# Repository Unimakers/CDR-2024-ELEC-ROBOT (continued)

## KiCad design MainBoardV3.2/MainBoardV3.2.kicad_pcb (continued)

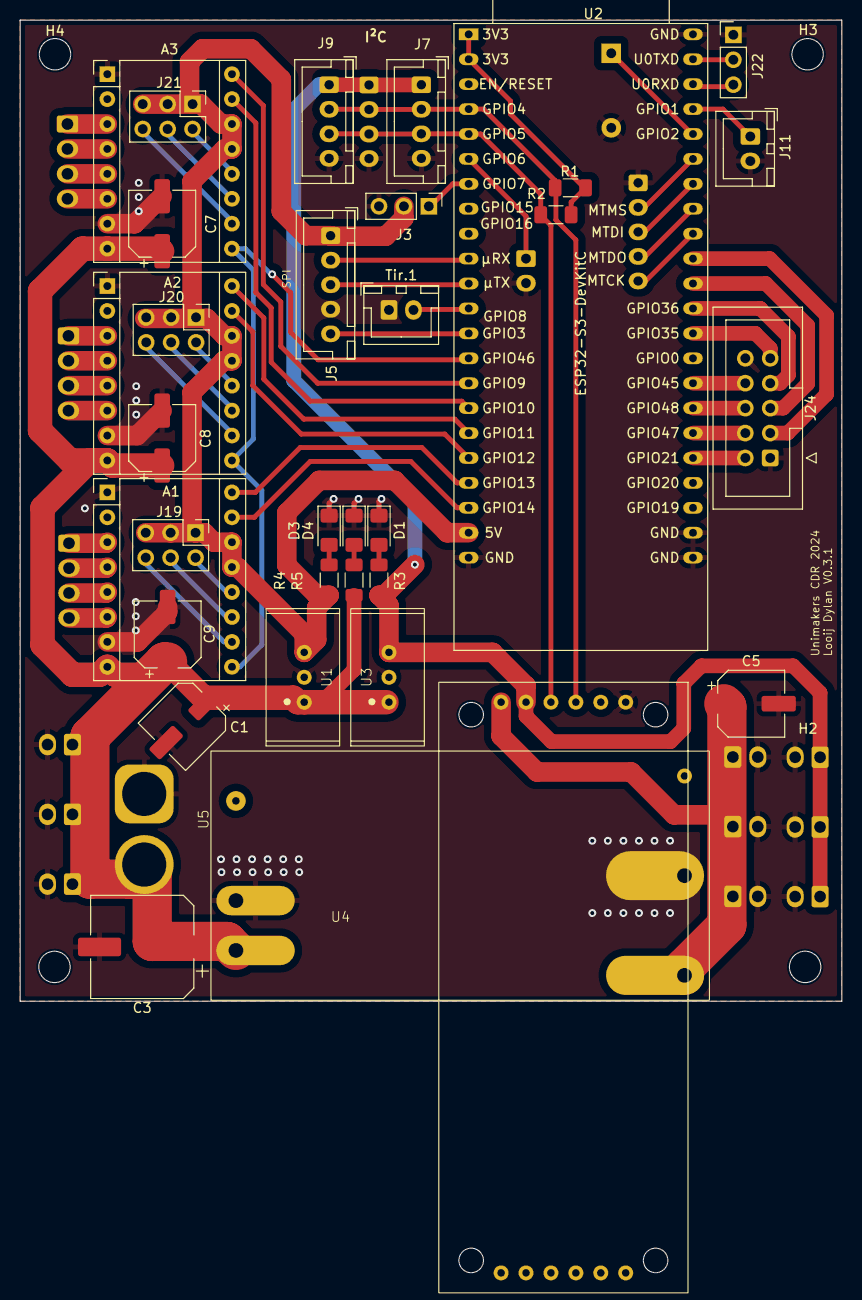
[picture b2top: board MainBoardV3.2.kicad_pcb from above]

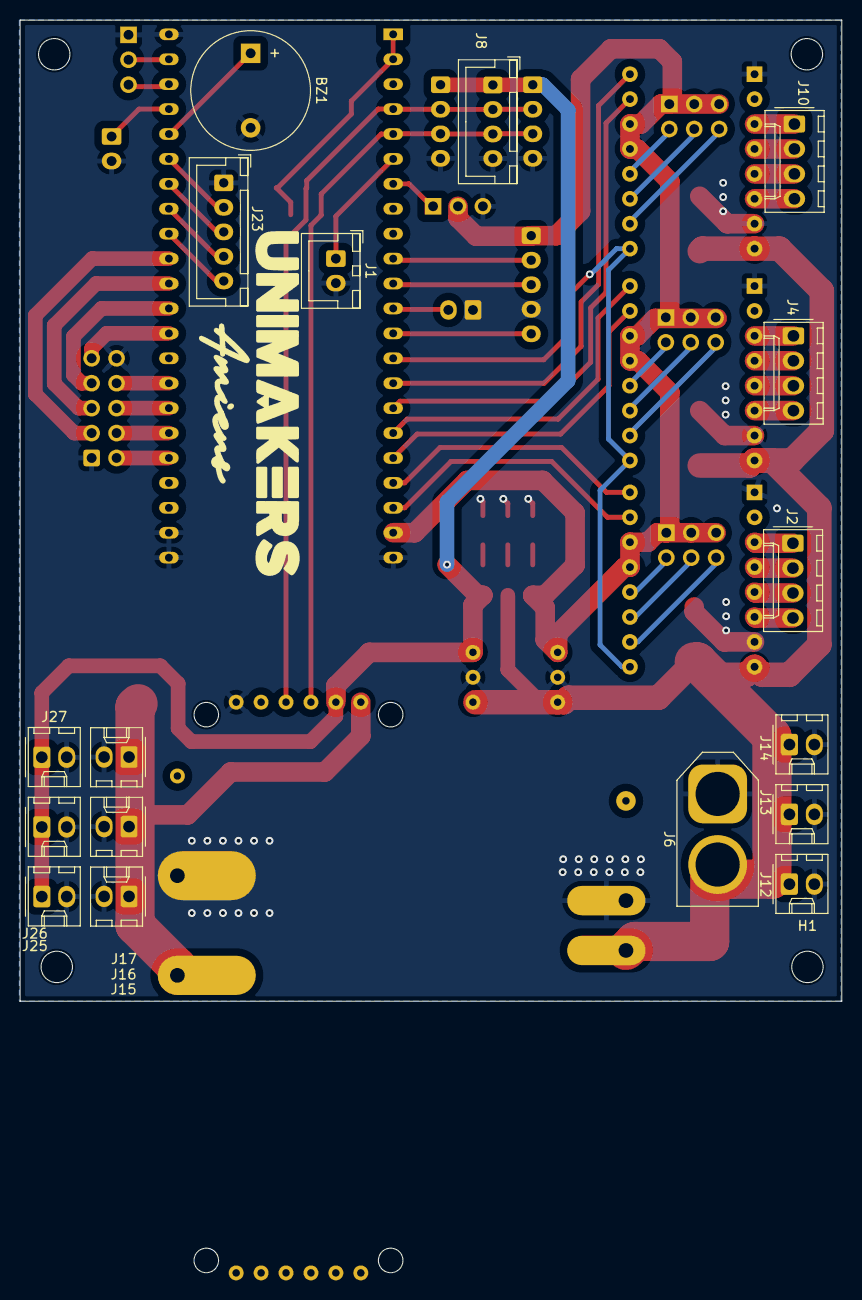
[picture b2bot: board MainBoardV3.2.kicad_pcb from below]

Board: 2 copper layers, 83.7 x 100.0 mm, 54 parts (18 on the bottom side), 61 nets.

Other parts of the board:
A2: Pololu_Breakout_DRV8825; Pololu_Breakout-16_15.2x20.3mm
D1, D3: LED_Small; LED_1206_3216Metric_Pad1.42x1.75mm_HandSolder
R3, R4: R_Small; R_1206_3216Metric_Pad1.30x1.75mm_HandSolder

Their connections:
DIR2: A2.16 (DIR); also elsewhere on the board
EN: A2.9 (~EN); also elsewhere on the board
GND: A2.1 (GND), A2.7 (GND), D1.1 (K), D3.1 (K); also elsewhere on the board
unnamed 28: A2.4 (A1); also elsewhere on the board
unnamed 29: A2.3 (A2); also elsewhere on the board
unnamed 30: A2.5 (B1); also elsewhere on the board
unnamed 31: A2.6 (B2); also elsewhere on the board
unnamed 32: A2.10 (M0); also elsewhere on the board
unnamed 33: A2.11 (M1); also elsewhere on the board
unnamed 34: A2.12 (M2); also elsewhere on the board
unnamed: D1.2 (A), R3.2
unnamed: D3.2 (A), R4.2
STEP2: A2.15 (STEP); also elsewhere on the board

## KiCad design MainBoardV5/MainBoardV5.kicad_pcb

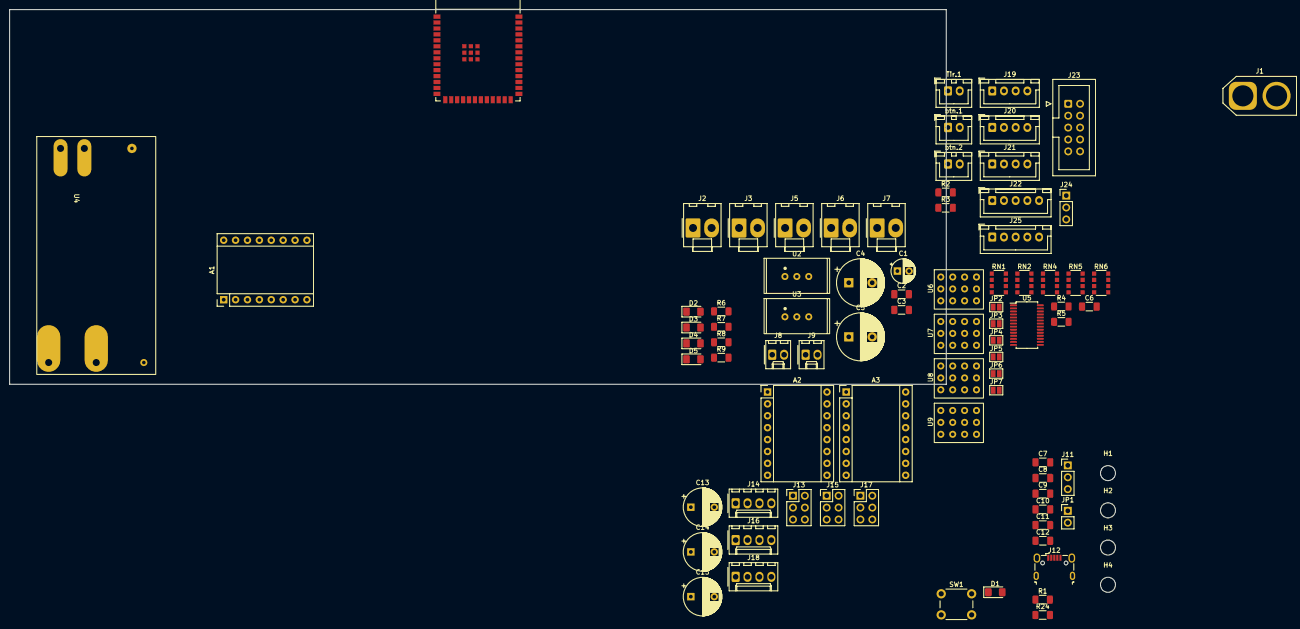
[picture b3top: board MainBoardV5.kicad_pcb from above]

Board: 4 copper layers, 200.0 x 80.0 mm, 85 parts (0 on the bottom side), 104 nets, no tracks yet.

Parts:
A1, A2, A3: Pololu_Breakout_DRV8825; Pololu_Breakout-16_15.2x20.3mm
C1: C_Polarized; CP_Radial_D5.0mm_P2.50mm
C2, C3, C6: C_Small; C_1206_3216Metric_Pad1.33x1.80mm_HandSolder
C4, C5: C_Polarized; CP_Radial_D10.0mm_P5.00mm
C7, C8, C9, C10, C11, C12: C; C_1206_3216Metric_Pad1.33x1.80mm_HandSolder
C13, C14, C15: C_Polarized; CP_Radial_D8.0mm_P5.00mm
D1, D2, D3, D4, D5: LED_Small; LED_1206_3216Metric_Pad1.42x1.75mm_HandSolder
H1, H2, H3, H4: MountingHole; MountingHole_3.2mm_M3
J1: Conn_01x02; AMASS_XT60-M_1x02_P7.20mm_Vertical
J2, J3, J5, J6, J7: Conn_01x02; Molex_KK-396_A-41791-0002_1x02_P3.96mm_Vertical
J8, J9: Conn_01x02; Molex_KK-254_AE-6410-02A_1x02_P2.54mm_Vertical
J11, J24: Conn_01x03; PinHeader_1x03_P2.54mm_Vertical
J12: USB_B_Micro; USB_Micro-B_Wuerth_629105150521
J13, J15, J17: Conn_02x03_Odd_Even; PinHeader_2x03_P2.54mm_Vertical
J14, J16, J18: Conn_01x04; Molex_KK-254_AE-6410-04A_1x04_P2.54mm_Vertical
J19, J20, J21: Conn_01x04; JST_XH_B4B-XH-A_1x04_P2.50mm_Vertical
J22, J25: Conn_01x05; JST_XH_B5B-XH-A_1x05_P2.50mm_Vertical
J23: Conn_02x05_Odd_Even; IDC-Header_2x05_P2.54mm_Vertical
JP1: Jumper_2_Open; PinHeader_1x02_P2.54mm_Vertical
JP2, JP3, JP4, JP5, JP6, JP7: Jumper_2_Open; SolderJumper-2_P1.3mm_Open_Pad1.0x1.5mm
R1, R4, R5, R6, R7, R8, R9: R_Small; R_1206_3216Metric_Pad1.30x1.75mm_HandSolder
R2, R3, R24: R; R_1206_3216Metric_Pad1.30x1.75mm_HandSolder
RN1, RN2, RN4, RN5, RN6: R_Pack04; R_Array_Convex_4x1206
SW1: SW_Push; SW_PUSH_6mm
Tir.1: Conn_01x02; JST_XH_B2B-XH-A_1x02_P2.50mm_Vertical
U1: ESP32-S3-WROOM-1
U2: TSR_2-2433; Traco 2- 24xx
U3: TSR_2-2450; Traco 2- 24xx
U4: TEN_50-2411WI; Traco TEN 50 series
U5: PCA9685PW; TSSOP-28_4.4x9.7mm_P0.65mm
U6, U7, U8, U9: Servo_Conn_Pack_x04; Servo_Bloc_x04
btn.1, btn.2: Conn_01x02; JST_XH_B2B-XH-A_1x02_P2.50mm_Vertical

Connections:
+3.3V: C6.2, J19.1, J20.1, J21.1, JP2.1 (A), JP3.1 (A), JP4.1 (A), JP5.1 (A), JP6.1 (A), JP7.1 (A), R2.1, R3.1, U5.28 (VDD)
+3V3: C2.1, C9.1, C10.1, R6.1, R24.1, U1.2 (3V3), U2.3 (VO)
+5V: A1.13 (~RST), A1.14 (~SLP), A2.13 (~RST), A2.14 (~SLP), A3.13 (~RST), A3.14 (~SLP), C3.1, J8.2, J9.2, J13.1, J13.3, J13.5, J15.1, J15.3, J15.5, J17.1, J17.3, J17.5, J22.1, R7.1, U3.3 (VO)
+5VP: C5.1, J5.2, J6.2, J7.2, J24.2, R8.1, U4.4 (+Vout), U6.1 (VCC), U7.1 (VCC), U8.1 (VCC), U9.1 (VCC)
+BATT: A1.8 (VMOT), A2.8 (VMOT), A3.8 (VMOT), C1.1, C4.1, C13.1, C14.1, C15.1, J1.2, J2.2, J3.2, R9.1, U2.1 (VI), U3.1 (VI), U4.1 (+Vin)
/Micro Proccessor/en: C11.1, C12.1, R24.2, SW1.2, U1.3 (EN)
Btn1: U1.5 (GPIO5/TOUCH5/ADC1_CH4), btn.1.2
Btn2: U1.6 (GPIO6/TOUCH6/ADC1_CH5), btn.2.2
DIR1: A1.16 (DIR), U1.20 (GPIO12/TOUCH12/ADC2_CH1/FSPICLK/FSPIIO6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)
DIR2: A2.16 (DIR), U1.18 (GPIO10/TOUCH10/ADC1_CH9/FSPICS0/FSPIIO4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)
DIR3: A3.16 (DIR), U1.15 (GPIO3/TOUCH3/ADC1_CH2)
EN: A1.9 (~EN), A2.9 (~EN), A3.9 (~EN), U1.22 (GPIO14/TOUCH14/ADC2_CH3/FSPIWP/FSPIDQS/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)
GND: A1.1 (GND), A1.7 (GND), A2.1 (GND), A2.7 (GND), A3.1 (GND), A3.7 (GND), C1.2, C2.2, C3.2, C4.2, C5.2, C6.1, C7.2, C8.2, C9.2, C10.2, C11.2, C12.2, C13.2, C14.2, C15.2, D1.1 (K), D2.1 (K), D3.1 (K), D4.1 (K), D5.1 (K), J1.1, J2.1, J3.1, J5.1, J6.1, J7.1, J8.1, J9.1, J11.3, J12.5 (GND), J12.6 (Shield), J19.4, J20.4, J21.4, J22.4, J23.1, J23.10, J24.3, J25.1, JP1.2 (B), R4.2, R5.2, RN2.1 (R1.1), RN2.2 (R2.1), RN2.3 (R3.1), RN2.4 (R4.1), SW1.1, Tir.1.1, U1.1 (GND), U1.40 (GND), U1.41 (GND), U2.2 (GND), U3.2 (GND), U4.2 (-Vin), U4.5 (-Vout), U5.14 (VSS), U5.25 (EXTCLK), U6.2 (GND), U7.2 (GND), U8.2 (GND), U9.2 (GND), btn.1.1, btn.2.1
LIDARRX: J22.2, U1.10 (GPIO17/U1TXD/ADC2_CH6)
LIDARTX: J22.3, U1.11 (GPIO18/U1RXD/ADC2_CH7/CLK_OUT3)
Nappe1: J23.8, U1.39 (GPIO1/TOUCH1/ADC1_CH0)
Nappe2: J23.6, U1.38 (GPIO2/TOUCH2/ADC1_CH1)
Nappe3: J23.4, U1.31 (GPIO38/FSPIWP/SUBSPIWP)
Nappe4: J23.2, U1.30 (SPIDQS/GPIO37/FSPIQ/SUBSPIQ)
Nappe5: J23.9, U1.25 (GPIO48/SPICLK_N/SUBSPICLK_N_DIFF)
Nappe6: J23.7, U1.26 (GPIO45)
Nappe7: J23.5, U1.28 (SPIIO6/GPIO35/FSPID/SUBSPID)
Nappe8: J23.3, U1.29 (SPIIO7/GPIO36/FSPICLK/SUBSPICLK)
Neopixel: J24.1, U1.7 (GPIO7/TOUCH7/ADC1_CH6)
unnamed: A1.4 (A1), J14.2
unnamed: A1.3 (A2), J14.1
unnamed: A1.5 (B1), J14.3
unnamed: A1.6 (B2), J14.4
unnamed: A1.10 (M0), J13.6
unnamed: A1.11 (M1), J13.4
unnamed: A1.12 (M2), J13.2
unnamed: A2.4 (A1), J16.2
unnamed: A2.3 (A2), J16.1
unnamed: A2.5 (B1), J16.3
unnamed: A2.6 (B2), J16.4
unnamed: A2.10 (M0), J15.6
unnamed: A2.11 (M1), J15.4
unnamed: A2.12 (M2), J15.2
unnamed: A3.4 (A1), J18.2
unnamed: A3.3 (A2), J18.1
unnamed: A3.5 (B1), J18.3
unnamed: A3.6 (B2), J18.4
unnamed: A3.10 (M0), J17.6
unnamed: A3.11 (M1), J17.4
unnamed: A3.12 (M2), J17.2
unnamed: D1.2 (A), R1.1
unnamed: D2.2 (A), R6.2
unnamed: D3.2 (A), R7.2
unnamed: D4.2 (A), R8.2
unnamed: D5.2 (A), R9.2
unnamed: J11.1, U1.37 (U0TXD/GPIO43/CLK_OUT1)
unnamed: J11.2, U1.36 (U0RXD/GPIO44/CLK_OUT2)
unnamed: C8.1, J12.3 (D+), U1.14 (GPIO20/U1CTS/ADC2_CH9/CLK_OUT1/USB_D+)
unnamed: C7.1, J12.2 (D-), U1.13 (GPIO19/U1RTS/ADC2_CH8/CLK_OUT2/USB_D-)
unnamed: J12.1 (VBUS), R1.2
unnamed: JP1.1 (A), U1.27 (GPIO0/BOOT)
unnamed: JP2.2 (B), RN2.8 (R1.2), U5.1 (A0)
unnamed: JP3.2 (B), RN2.7 (R2.2), U5.2 (A1)
unnamed: JP4.2 (B), RN2.6 (R3.2), U5.3 (A2)
unnamed: JP5.2 (B), RN2.5 (R4.2), U5.4 (A3)
unnamed: JP6.2 (B), R4.1, U5.5 (A4)
unnamed: JP7.2 (B), R5.1, U5.24 (A5)
unnamed: RN1.1 (R1.1), U5.9 (LED3)
unnamed: RN1.8 (R1.2), U6.6 (Servo1)
unnamed: RN1.2 (R2.1), U5.8 (LED2)
unnamed: RN1.7 (R2.2), U6.5 (Servo1)
unnamed: RN1.3 (R3.1), U5.7 (LED1)
unnamed: RN1.6 (R3.2), U6.4 (Servo1)
unnamed: RN1.4 (R4.1), U5.6 (LED0)
unnamed: RN1.5 (R4.2), U6.3 (Servo1)
unnamed: RN4.1 (R1.1), U5.13 (LED7)
unnamed: RN4.8 (R1.2), U7.6 (Servo1)
unnamed: RN4.2 (R2.1), U5.12 (LED6)
unnamed: RN4.7 (R2.2), U7.5 (Servo1)
unnamed: RN4.3 (R3.1), U5.11 (LED5)
unnamed: RN4.6 (R3.2), U7.4 (Servo1)
unnamed: RN4.4 (R4.1), U5.10 (LED4)
unnamed: RN4.5 (R4.2), U7.3 (Servo1)
unnamed: RN5.1 (R1.1), U5.18 (LED11)
unnamed: RN5.8 (R1.2), U8.6 (Servo1)
unnamed: RN5.2 (R2.1), U5.17 (LED10)
unnamed: RN5.7 (R2.2), U8.5 (Servo1)
unnamed: RN5.3 (R3.1), U5.16 (LED9)
unnamed: RN5.6 (R3.2), U8.4 (Servo1)
unnamed: RN5.4 (R4.1), U5.15 (LED8)
unnamed: RN5.5 (R4.2), U8.3 (Servo1)
unnamed: RN6.1 (R1.1), U5.22 (LED15)
unnamed: RN6.8 (R1.2), U9.6 (Servo1)
unnamed: RN6.2 (R2.1), U5.21 (LED14)
unnamed: RN6.7 (R2.2), U9.5 (Servo1)
unnamed: RN6.3 (R3.1), U5.20 (LED13)
unnamed: RN6.6 (R3.2), U9.4 (Servo1)
unnamed: RN6.4 (R4.1), U5.19 (LED12)
unnamed: RN6.5 (R4.2), U9.3 (Servo1)
SCL: J19.2, J20.2, J21.2, R2.2, U1.17 (GPIO9/TOUCH9/ADC1_CH8/FSPIHD/SUBSPIHD), U5.26 (SCL)
SDA: J19.3, J20.3, J21.3, R3.2, U1.12 (GPIO8/TOUCH8/ADC1_CH7/SUBSPICS1), U5.27 (SDA)
SPICLK: J25.2, U1.32 (MTCK/GPIO39/CLK_OUT3/SUBSPICS1)
SPIDI: J25.4, U1.34 (MTDI/GPIO41/CLK_OUT1)
SPIDO: J25.3, U1.33 (MTDO/GPIO40/CLK_OUT2)
SPIMS: J25.5, U1.35 (MTMS/GPIO42)
STEP1: A1.15 (STEP), U1.21 (GPIO13/TOUCH13/ADC2_CH2/FSPIQ/FSPIIO7/S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)
STEP2: A2.15 (STEP), U1.19 (GPIO11/TOUCH11/ADC2_CH0/FSPID/FSPIIO5/S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)
STEP3: A3.15 (STEP), U1.16 (GPIO46)
Tir.: Tir.1.2, U1.4 (GPIO4/TOUCH4/ADC1_CH3)

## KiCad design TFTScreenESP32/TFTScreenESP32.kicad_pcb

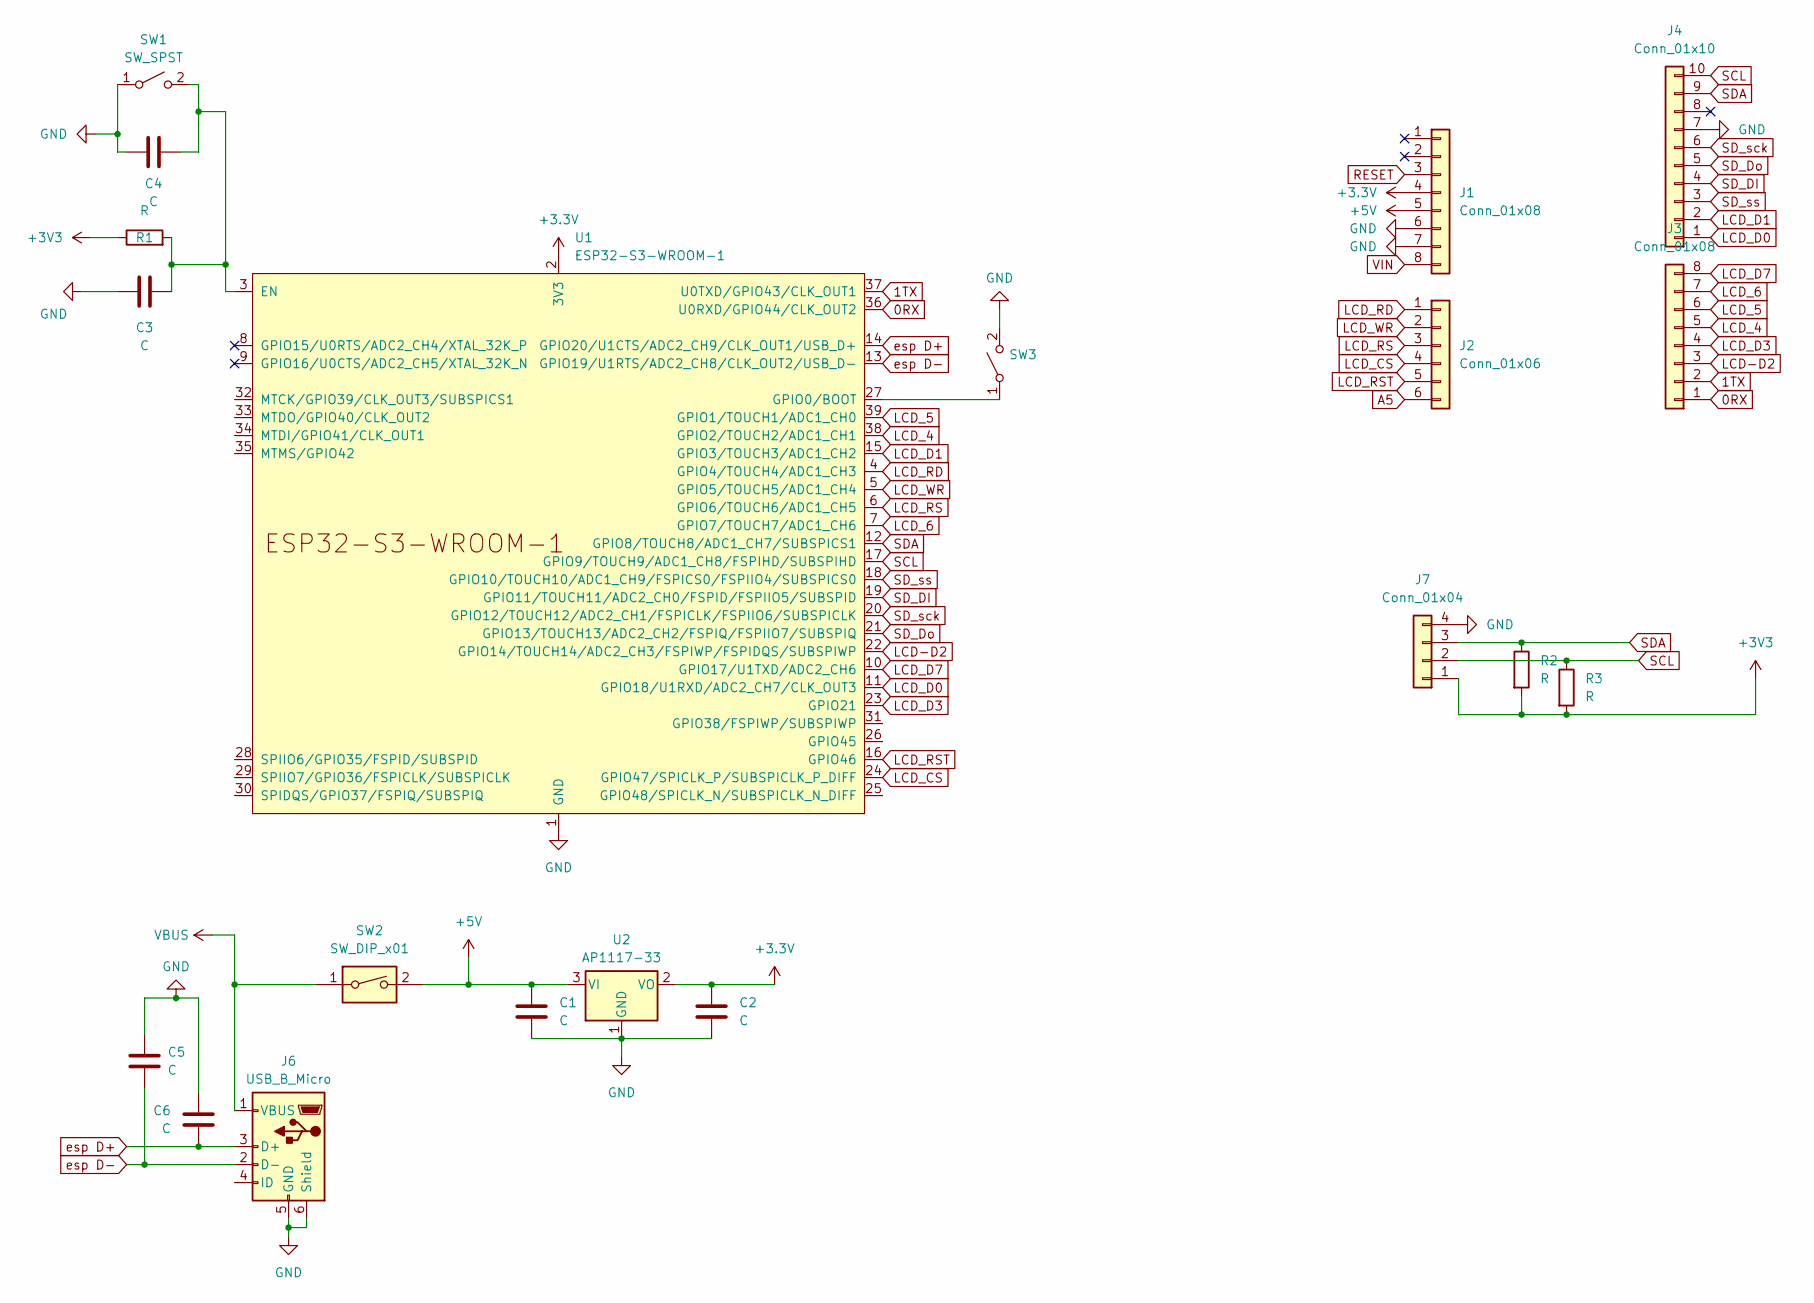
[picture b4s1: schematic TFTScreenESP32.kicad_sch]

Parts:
C1, C2, C3, C4, C5, C6: C; C_1206_3216Metric_Pad1.33x1.80mm_HandSolder
J1, J3: Conn_01x08; PinSocket_1x08_P2.54mm_Vertical
J2: Conn_01x06; PinSocket_1x06_P2.54mm_Vertical
J4: Conn_01x10; PinSocket_1x10_P2.54mm_Vertical
J6: USB_B_Micro; USB_Micro-B_Molex-105017-0001
J7: Conn_01x04; JST_XH_B4B-XH-A_1x04_P2.50mm_Vertical
R1, R2, R3: R; R_1206_3216Metric_Pad1.30x1.75mm_HandSolder
SW1, SW3: SW_SPST; PinSocket_1x02_P2.54mm_Vertical
SW2: SW_DIP_x01; SW_DIP_SPSTx01_Slide_9.78x4.72mm_W7.62mm_P2.54mm
U1: ESP32-S3-WROOM-1
U2: AP1117-33; SOT-223-3_TabPin2

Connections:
0RX: J3.1, U1.36 (U0RXD/GPIO44/CLK_OUT2)
1TX: J3.2, U1.37 (U0TXD/GPIO43/CLK_OUT1)
+5V: C1.1, J1.5, SW2.2, U2.3 (VI)
A5: J2.6
GND: C1.2, C2.2, C3.2, C4.2, C5.2, C6.1, J1.6, J1.7, J4.7, J6.5 (GND), J6.6 (Shield), J7.4, SW1.1 (A), SW3.2 (B), U1.1 (GND), U1.40 (GND), U1.41 (GND), U2.1 (GND)
LCD-D2: J3.3, U1.22 (GPIO14/TOUCH14/ADC2_CH3/FSPIWP/FSPIDQS/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)
LCD_4: J3.5, U1.38 (GPIO2/TOUCH2/ADC1_CH1)
LCD_5: J3.6, U1.39 (GPIO1/TOUCH1/ADC1_CH0)
LCD_6: J3.7, U1.7 (GPIO7/TOUCH7/ADC1_CH6)
LCD_CS: J2.4, U1.24 (GPIO47/SPICLK_P/SUBSPICLK_P_DIFF)
LCD_D0: J4.1, U1.11 (GPIO18/U1RXD/ADC2_CH7/CLK_OUT3)
LCD_D1: J4.2, U1.15 (GPIO3/TOUCH3/ADC1_CH2)
LCD_D3: J3.4, U1.23 (GPIO21)
LCD_D7: J3.8, U1.10 (GPIO17/U1TXD/ADC2_CH6)
LCD_RD: J2.1, U1.4 (GPIO4/TOUCH4/ADC1_CH3)
LCD_RS: J2.3, U1.6 (GPIO6/TOUCH6/ADC1_CH5)
LCD_RST: J2.5, U1.16 (GPIO46)
LCD_WR: J2.2, U1.5 (GPIO5/TOUCH5/ADC1_CH4)
unnamed: C3.1, C4.1, R1.2, SW1.2 (B), U1.3 (EN)
unnamed: SW3.1 (A), U1.27 (GPIO0/BOOT)
RESET: J1.3
SCL: J4.10, J7.2, R3.1, U1.17 (GPIO9/TOUCH9/ADC1_CH8/FSPIHD/SUBSPIHD)
SDA: J4.9, J7.3, R2.1, U1.12 (GPIO8/TOUCH8/ADC1_CH7/SUBSPICS1)
SD_DI: J4.4, U1.19 (GPIO11/TOUCH11/ADC2_CH0/FSPID/FSPIIO5/S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)
SD_Do: J4.5, U1.21 (GPIO13/TOUCH13/ADC2_CH2/FSPIQ/FSPIIO7/S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)
SD_sck: J4.6, U1.20 (GPIO12/TOUCH12/ADC2_CH1/FSPICLK/FSPIIO6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)
SD_ss: J4.3, U1.18 (GPIO10/TOUCH10/ADC1_CH9/FSPICS0/FSPIIO4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)
VBUS: J6.1 (VBUS), SW2.1
VIN: J1.8
esp D+: C6.2, J6.3 (D+), U1.14 (GPIO20/U1CTS/ADC2_CH9/CLK_OUT1/USB_D+)
esp D-: C5.1, J6.2 (D-), U1.13 (GPIO19/U1RTS/ADC2_CH8/CLK_OUT2/USB_D-)

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
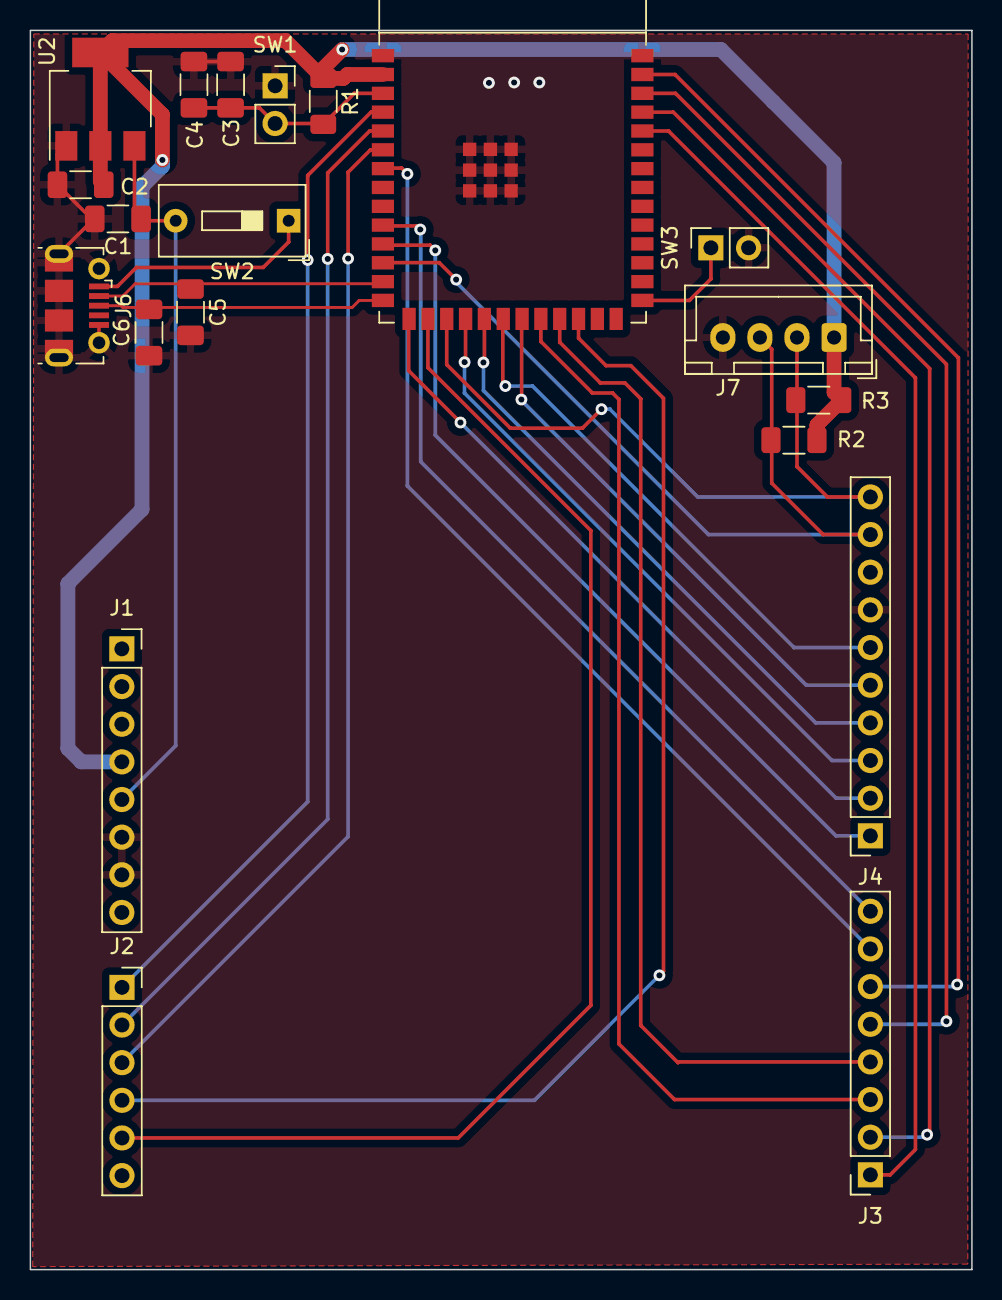
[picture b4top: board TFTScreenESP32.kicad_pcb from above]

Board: 2 copper layers, 63.5 x 83.6 mm, 20 parts (0 on the bottom side), 29 nets.

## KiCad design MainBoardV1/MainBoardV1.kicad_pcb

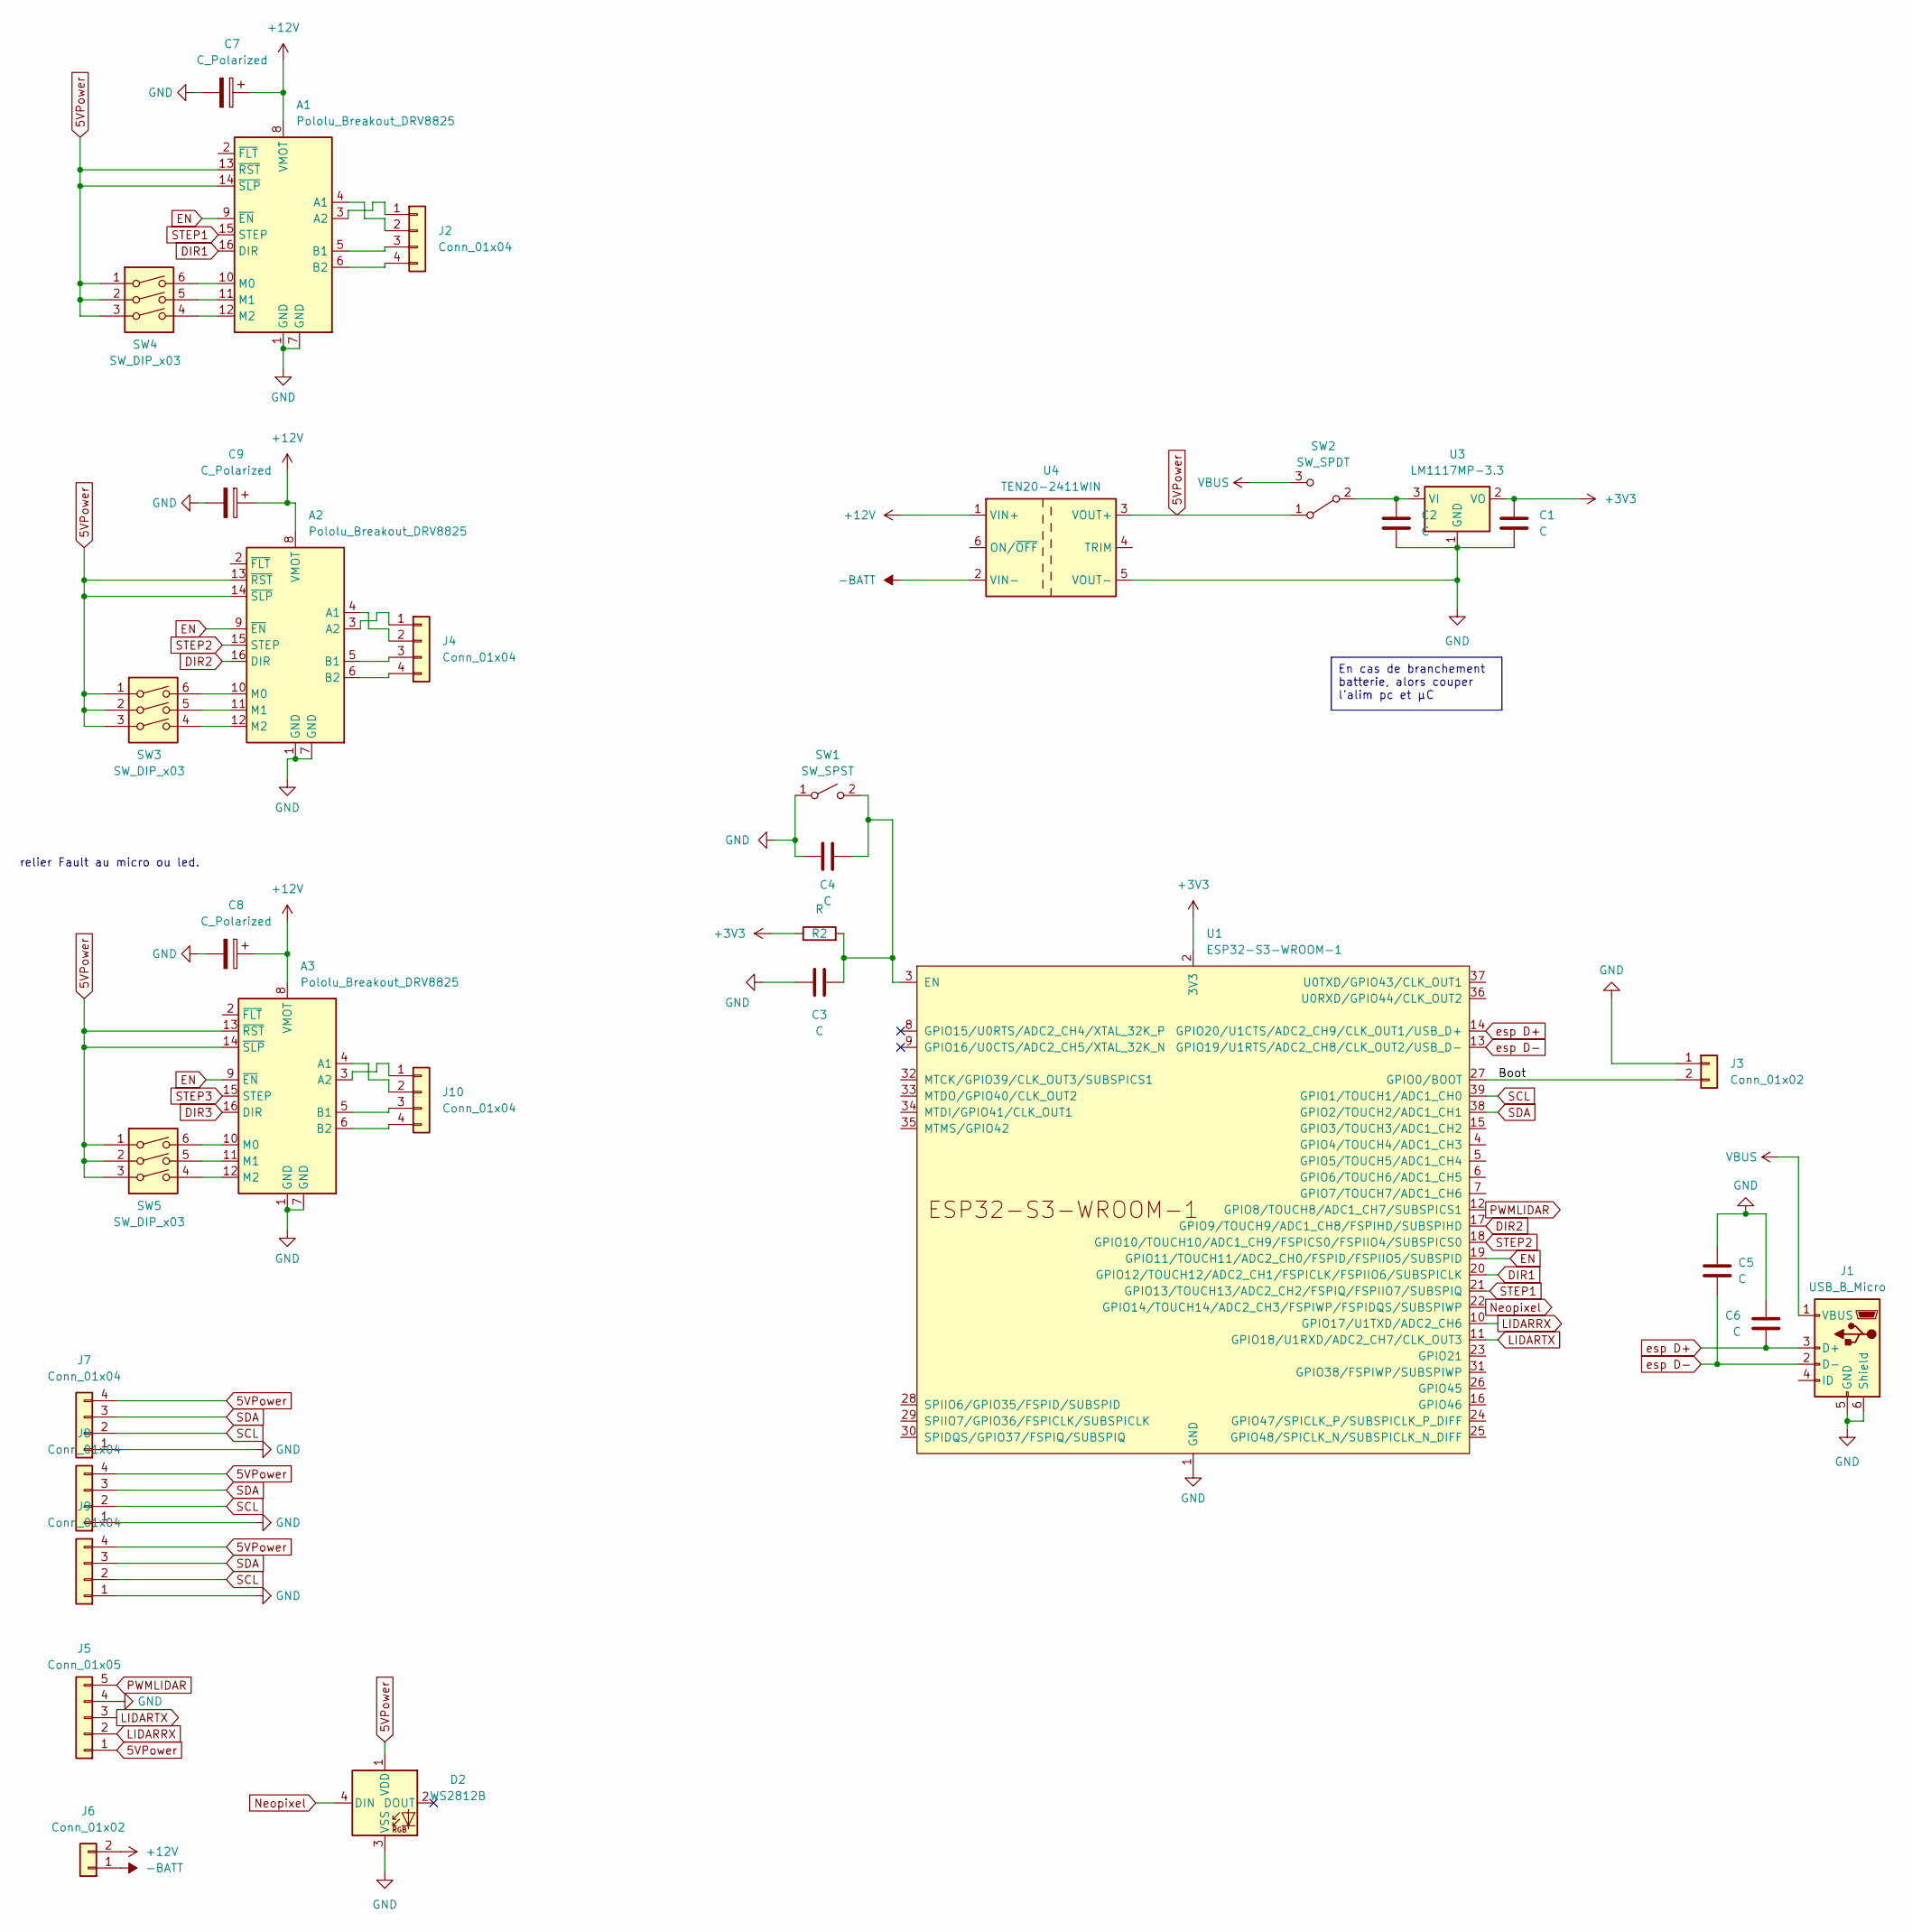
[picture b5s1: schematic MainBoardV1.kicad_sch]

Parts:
A1, A2, A3: Pololu_Breakout_DRV8825; Pololu_Breakout-16_15.2x20.3mm
C1, C2, C3, C4, C5, C6: C; C_1206_3216Metric_Pad1.33x1.80mm_HandSolder
C7, C8, C9: C_Polarized; CP_Radial_D8.0mm_P3.50mm
D2: WS2812B; LED_WS2812B_PLCC4_5.0x5.0mm_P3.2mm
J1: USB_B_Micro; USB_Micro-B_Molex-105017-0001
J2, J4, J7, J8, J9, J10: Conn_01x04; JST_XH_B4B-XH-A_1x04_P2.50mm_Vertical
J3: Conn_01x02; PinHeader_1x02_P2.54mm_Vertical
J5: Conn_01x05; JST_XH_B5B-XH-A_1x05_P2.50mm_Vertical
J6: Conn_01x02; TerminalBlock_Altech_AK300-2_P5.00mm
R2: R; R_1206_3216Metric_Pad1.30x1.75mm_HandSolder
SW1: SW_SPST; PinSocket_1x02_P2.54mm_Vertical
SW2: SW_SPDT; PinSocket_1x03_P2.54mm_Vertical
SW3, SW4, SW5: SW_DIP_x03; SW_DIP_SPSTx03_Slide_9.78x9.8mm_W8.61mm_P2.54mm
U1: ESP32-S3-WROOM-1
U3: LM1117MP-3.3; SOT-223-3_TabPin2
U4: TEN20-2411WIN; Converter_DCDC_TRACO_TEN20-xxxx_THT

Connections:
5VPower: A1.13 (~RST), A1.14 (~SLP), A2.13 (~RST), A2.14 (~SLP), A3.13 (~RST), A3.14 (~SLP), D2.1 (VDD), J5.1, J7.4, J8.4, J9.4, SW2.1 (A), SW3.1, SW3.2, SW3.3, SW4.1, SW4.2, SW4.3, SW5.1, SW5.2, SW5.3, U4.3 (VOUT+)
+3V3: C1.1, R2.1, U1.2 (3V3), U3.2 (VO)
+12V: A1.8 (VMOT), A2.8 (VMOT), A3.8 (VMOT), C7.1, C8.1, C9.1, J6.2, U4.1 (VIN+)
-BATT: J6.1, U4.2 (VIN-)
/Boot: J3.2, U1.27 (GPIO0/BOOT)
DIR1: A1.16 (DIR), U1.20 (GPIO12/TOUCH12/ADC2_CH1/FSPICLK/FSPIIO6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)
DIR2: A2.16 (DIR), U1.17 (GPIO9/TOUCH9/ADC1_CH8/FSPIHD/SUBSPIHD)
DIR3: A3.16 (DIR)
EN: A1.9 (~EN), A2.9 (~EN), A3.9 (~EN), U1.19 (GPIO11/TOUCH11/ADC2_CH0/FSPID/FSPIIO5/S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)
GND: A1.1 (GND), A1.7 (GND), A2.1 (GND), A2.7 (GND), A3.1 (GND), A3.7 (GND), C1.2, C2.2, C3.2, C4.2, C5.2, C6.1, C7.2, C8.2, C9.2, D2.3 (VSS), J1.5 (GND), J1.6 (Shield), J3.1, J5.4, J7.1, J8.1, J9.1, SW1.1 (A), U1.1 (GND), U1.40 (GND), U1.41 (GND), U3.1 (GND), U4.5 (VOUT-)
LIDARRX: J5.2, U1.10 (GPIO17/U1TXD/ADC2_CH6)
LIDARTX: J5.3, U1.11 (GPIO18/U1RXD/ADC2_CH7/CLK_OUT3)
Neopixel: D2.4 (DIN), U1.22 (GPIO14/TOUCH14/ADC2_CH3/FSPIWP/FSPIDQS/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)
unnamed: A1.4 (A1), J2.2
unnamed: A1.3 (A2), J2.1
unnamed: A1.5 (B1), J2.3
unnamed: A1.6 (B2), J2.4
unnamed: A1.10 (M0), SW4.6
unnamed: A1.11 (M1), SW4.5
unnamed: A1.12 (M2), SW4.4
unnamed: A2.4 (A1), J4.2
unnamed: A2.3 (A2), J4.1
unnamed: A2.5 (B1), J4.3
unnamed: A2.6 (B2), J4.4
unnamed: A2.10 (M0), SW3.6
unnamed: A2.11 (M1), SW3.5
unnamed: A2.12 (M2), SW3.4
unnamed: A3.4 (A1), J10.2
unnamed: A3.3 (A2), J10.1
unnamed: A3.5 (B1), J10.3
unnamed: A3.6 (B2), J10.4
unnamed: A3.10 (M0), SW5.6
unnamed: A3.11 (M1), SW5.5
unnamed: A3.12 (M2), SW5.4
unnamed: C3.1, C4.1, R2.2, SW1.2 (B), U1.3 (EN)
unnamed: C2.1, SW2.2 (B), U3.3 (VI)
PWMLIDAR: J5.5, U1.12 (GPIO8/TOUCH8/ADC1_CH7/SUBSPICS1)
SCL: J7.2, J8.2, J9.2, U1.39 (GPIO1/TOUCH1/ADC1_CH0)
SDA: J7.3, J8.3, J9.3, U1.38 (GPIO2/TOUCH2/ADC1_CH1)
STEP1: A1.15 (STEP), U1.21 (GPIO13/TOUCH13/ADC2_CH2/FSPIQ/FSPIIO7/S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)
STEP2: A2.15 (STEP), U1.18 (GPIO10/TOUCH10/ADC1_CH9/FSPICS0/FSPIIO4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)
STEP3: A3.15 (STEP)
VBUS: J1.1 (VBUS), SW2.3 (C)
esp D+: C6.2, J1.3 (D+), U1.14 (GPIO20/U1CTS/ADC2_CH9/CLK_OUT1/USB_D+)
esp D-: C5.1, J1.2 (D-), U1.13 (GPIO19/U1RTS/ADC2_CH8/CLK_OUT2/USB_D-)

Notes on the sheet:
En cas de branchement batterie, alors couper l'alim pc et µC
relier Fault au micro ou led.

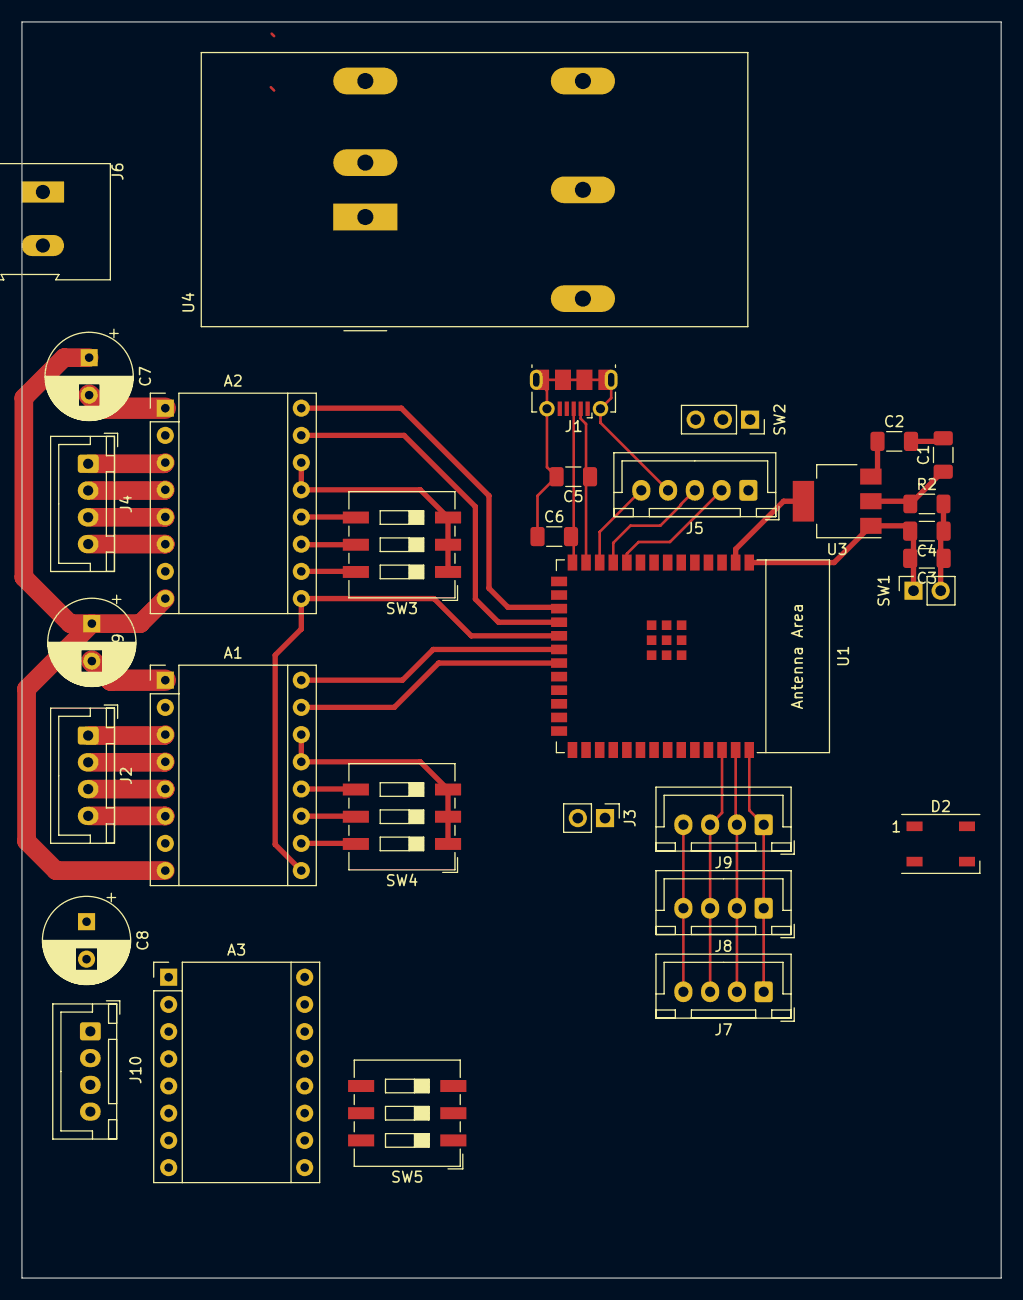
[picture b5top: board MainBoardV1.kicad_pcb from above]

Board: 2 copper layers, 91.4 x 117.3 mm, 32 parts (0 on the bottom side), 43 nets.

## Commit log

2023-10-21 Finished V2
    Finished V2, waiting for comfirmation for production
2023-10-21 Finishing touches, Added Ticker Lines
2023-10-22 Application des conseils discord
2023-10-31 Last desing of V2, and creation of V3
2023-10-31 TFTScreen
2023-10-31 Globalise Librarie
2023-11-01 TFTShieldAdaptor
2023-11-02 STEP+TFT
2023-11-11 La V3 en mode, je ne sais quoi
2023-11-11 hOLDUP
2023-11-11 Recup sur linux
2023-11-11 Maybe Vscode will solve the problem
2023-11-22 Mise a jour pour remi
2023-12-08 V0.4 modifications all components attached
2023-12-15 Apparition de V0.4
2024-01-02 V0.3.1 Finalizations
2024-01-02 test
2024-01-16 V3.1
2024-02-03 remove of V4 and V5 for fresh start
2024-03-10 Drc checks
2024-03-20 Mise a jour
